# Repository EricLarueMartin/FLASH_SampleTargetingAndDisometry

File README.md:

# FLASH Sample Targeting and Dosimetry

One device, one repository: the XY sample positioner and the DoseCam per-pulse beam
imager for the Duke FEL Lab FLASH rig (linac low-energy spectrometer, ~30 MeV electrons).
Both run on one Raspberry Pi 5 (`pi-06-ioc`) behind a single nginx site:
`/` DoseCam, `/motion/` positioning camera and manual moves, `/run/` automatic
position-and-fire, `/settings/` firing route.

This repository replaces the separate `SynchronizedCameraDosimeter` repository and the
`FLASH` working repository (motion code, stepper firmware, deploy files).

**Slides and documentation** (GitHub Pages; [deployment workflow](.github/workflows/pages.yml) publishes `/docs` from `main`):

- [DoseCam slides: dosimetry, fiducial positioning, CoreXY and automated runs](https://ericlaruemartin.github.io/FLASH_SampleTargetingAndDisometry/slides/2026-11-dosecam-film/)
- [All project slides and documentation](https://ericlaruemartin.github.io/FLASH_SampleTargetingAndDisometry/)

## Layout

| Path | What | Came from |
|---|---|---|
| `dose_cam/` | DoseCam Flask app (IMX296 external-trigger capture, beam fit, Files viewer). Its README is the full DoseCam operator/developer guide. | `SynchronizedCameraDosimeter/dose_cam`, `README.md` |
| `motor_control/` | Positioner web app: shared OV5647 camera stream, stepper link, loadout map, Run sequencer, firing gateway client | `FLASH/camera_stream` |
| `firmware/DDG/` | ESP8266 delayed shutter-pulse generator (Arduino sketch) | `SynchronizedCameraDosimeter/DDG` |
| `firmware/StepperController/` | ESP32 stepper controller (Arduino sketch). Passwords in `MyConfig.h` are redacted — set them before flashing. | `FLASH/StepperController` |
| `hardware/OptoIsolator/` | KiCad opto-isolator board for the laser charging pulse input | `SynchronizedCameraDosimeter/OptoIsolator` |
| `hardware/cad/` | Positioner / holder CAD (STEP, Fusion `.f3z`) | `FLASH/*.step`, `*.f3z` |
| `hardware/manuals/` | Component manuals | `SynchronizedCameraDosimeter/ComponentManuals` |
| `deploy/dosecam/` | DoseCam systemd, nginx, Wi-Fi isolation firewall | `SynchronizedCameraDosimeter/deploy` |
| `deploy/combined-pi/` | Combined-Pi additions: motor_control service + drop-in, merged nginx site, `config.txt` snippet | `FLASH/deploy/combined-pi` |
| `deploy/fire-gateway/` | Forced-command SSH gateway for live firing | `FLASH/deploy/fire-gateway` |
| `tools/dosecam/` | Bench probes, analysis scripts, tests for DoseCam | `SynchronizedCameraDosimeter/tools` |
| `tools/faraday_cup/` | Faraday-cup digitizer bench tools | `FLASH/fc_digitizer/tools` |
| `docs/` | GitHub Pages root: slides, analysis notes, wiring diagrams, roadmap, history logs | both |
| `docs/history/` | Detailed change logs: `DOSECAM_AGENT_LOG.md` (was `AGENT.md`), `COMBINE_SINGLE_PI.md` | both |

## Install paths on the Pi are unchanged

The deployed services still run from their old install locations — this reorganisation
changes the repository only:

- DoseCam: `/home/codex/SynchronizedCameraDosimeter/dose_cam` (`dose-cam.service`, nginx :80 → Flask :8000)
- Positioner: `/home/test/camera_stream` (`motor_control.service`, 127.0.0.1:8081)

When redeploying from this repo, copy `dose_cam/` and `motor_control/` to those paths (or
update the unit files in `deploy/` together with the new paths).
Paths such as `DDG/DDG.ino` or `tools/…` inside `dose_cam/README.md` refer to the old
repository layout; use the table above.

## Safety

This system interfaces with accelerator timing and controls. Do not connect facility timing
signals, change beamline hardware, or write accelerator PVs without approval from responsible
Duke/FELL personnel. Treat dose output as experimental until calibrated.

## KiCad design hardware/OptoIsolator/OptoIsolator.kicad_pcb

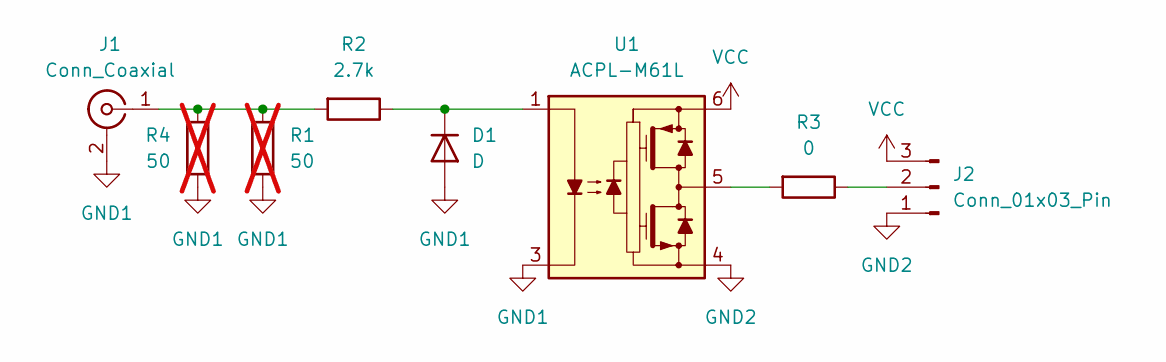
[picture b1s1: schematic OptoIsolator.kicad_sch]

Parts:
D1: D; D_SOD-123F
J1: Conn_Coaxial; BNC_Amphenol_B6252HB-NPP3G-50_Horizontal
J2: Conn_01x03_Pin; PinHeader_1x03_P2.54mm_Horizontal
R1, R4: 50; R_1206_3216Metric; not fitted
R2: 2.7k; R_0805_2012Metric
R3: 0; R_0805_2012Metric
U1: ACPL-M61L; SO-5-6_4.55x3.7mm_P1.27mm

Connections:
GND1: D1.2 (A), J1.2 (Ext), R1.2, R4.2, U1.3 (C)
GND2: J2.1, U1.4 (VEE)
unnamed: D1.1 (K), R2.1, U1.1 (A)
unnamed: J1.1 (In), R1.1, R2.2, R4.1
unnamed: J2.2, R3.1
unnamed: R3.2, U1.5 (VO)
VCC: J2.3, U1.6 (VCC)

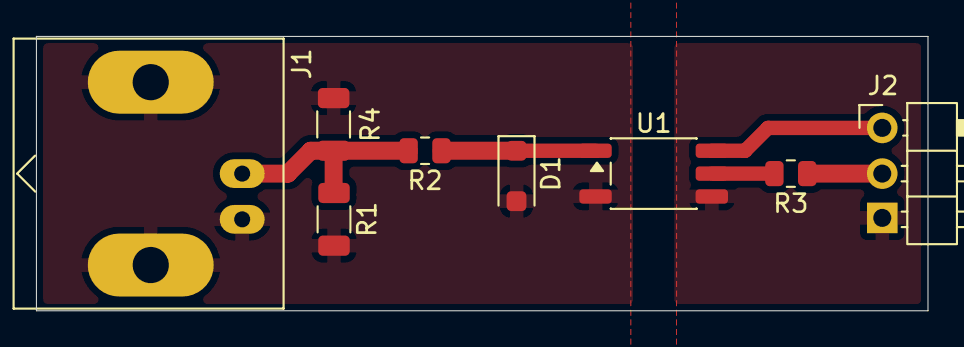
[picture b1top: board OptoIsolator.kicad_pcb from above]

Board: 2 copper layers, 49.5 x 15.2 mm, 8 parts (0 on the bottom side), 7 nets.
